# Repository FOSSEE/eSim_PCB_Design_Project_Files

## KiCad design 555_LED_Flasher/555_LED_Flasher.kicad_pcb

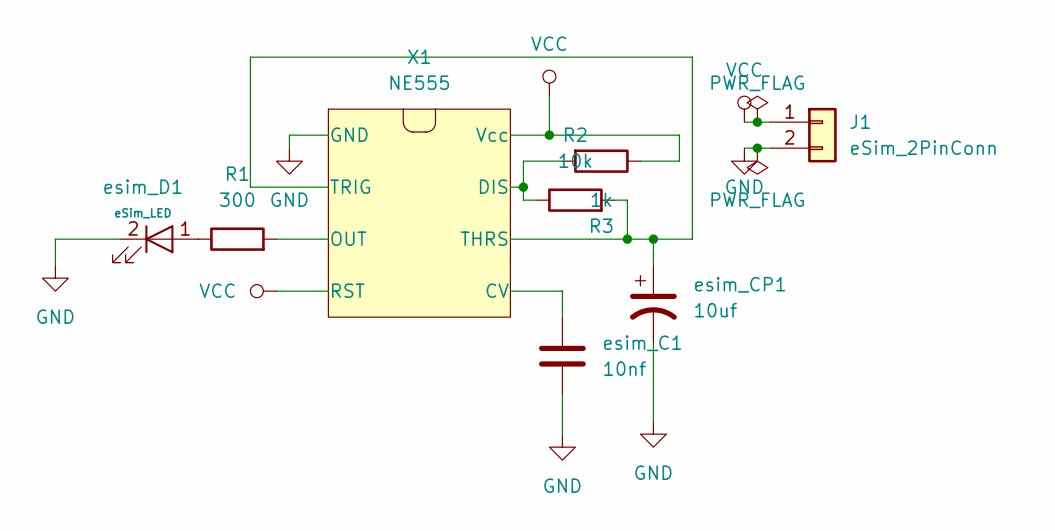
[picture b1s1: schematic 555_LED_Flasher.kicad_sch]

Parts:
J1: eSim_2PinConn; PinHeader_1x02_P2.54mm_Vertical
R1: 300; R_Axial_DIN0207_L6.3mm_D2.5mm_P10.16mm_Horizontal
R2: 10k; R_Axial_DIN0207_L6.3mm_D2.5mm_P10.16mm_Horizontal
R3: 1k; R_Axial_DIN0207_L6.3mm_D2.5mm_P10.16mm_Horizontal
X1: NE555; DIP-8_W7.62mm
esim_C1: 10nf; C_Disc_D5.0mm_W2.5mm_P5.00mm
esim_CP1: 10uf; CP_Radial_D5.0mm_P2.00mm
esim_D1: eSim_LED; LED_D5.0mm_Clear

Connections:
GND: J1.2, X1.1 (GND), esim_C1.2, esim_CP1.2, esim_D1.2 (K)
unnamed: X1.5 (CV), esim_C1.1
unnamed: R2.1, R3.2, X1.7 (DIS)
unnamed: R1.2, X1.3 (OUT)
unnamed: R2.2, X1.2 (TRIG), X1.6 (THRS), esim_CP1.1
unnamed: R1.1, esim_D1.1 (A)
VCC: J1.1, R3.1, X1.4 (RST), X1.8 (Vcc)

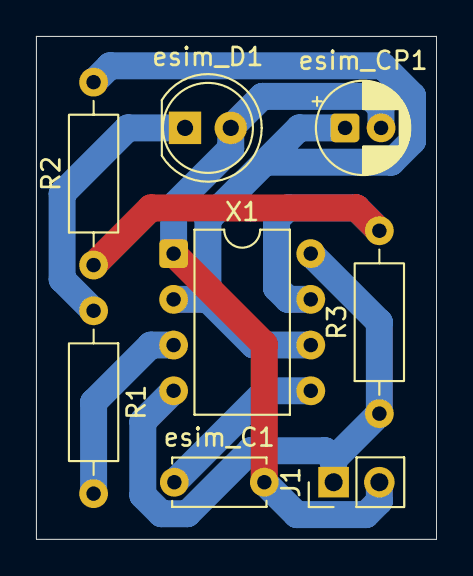
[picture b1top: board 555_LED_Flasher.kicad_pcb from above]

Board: 2 copper layers, 22.2 x 27.9 mm, 8 parts (0 on the bottom side), 7 nets.

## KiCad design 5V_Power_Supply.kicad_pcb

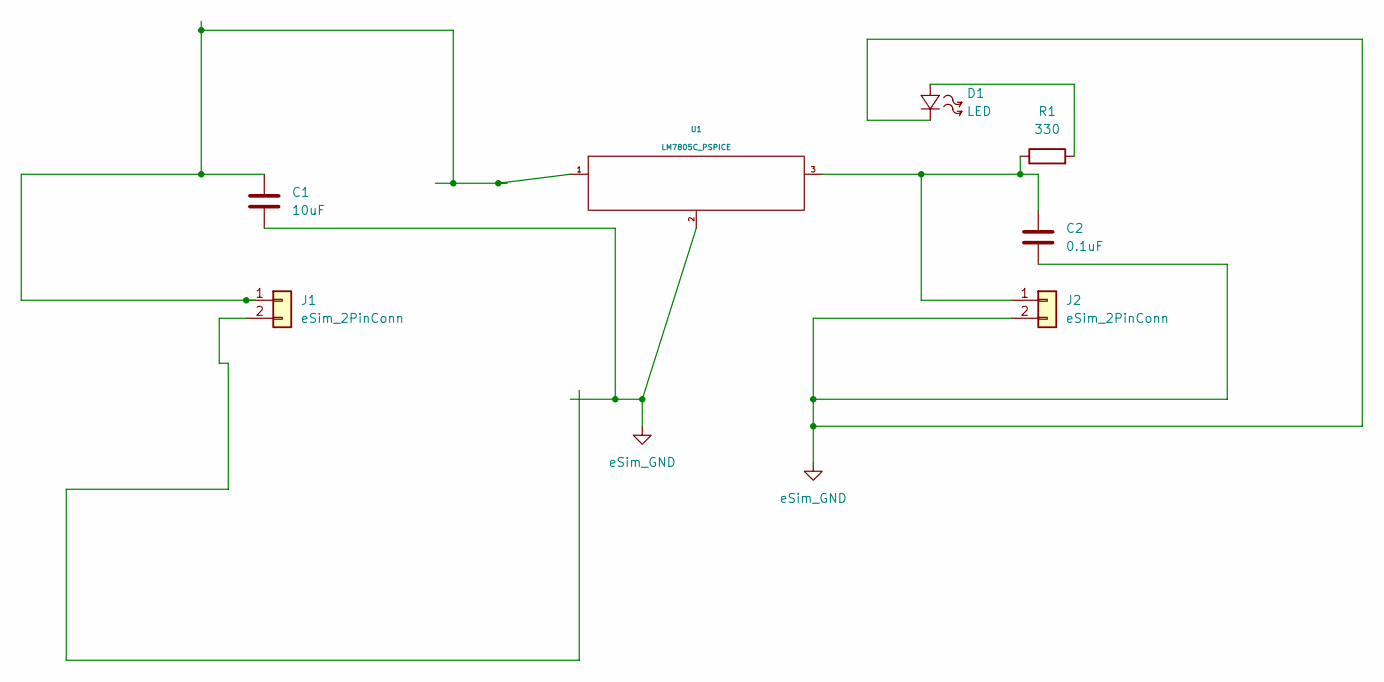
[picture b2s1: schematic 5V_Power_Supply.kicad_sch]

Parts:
C1: 10uF; C_Radial_D5.0mm_H7.0mm_P2.00mm
C2: 0.1uF; C_Disc_D5.0mm_W2.5mm_P5.00mm
D1: LED; LED_D5.0mm_Clear
J1, J2: eSim_2PinConn; PinHeader_1x02_P2.54mm_Vertical
R1: 330; R_Axial_DIN0207_L6.3mm_D2.5mm_P10.16mm_Horizontal
U1: LM7805C_PSPICE; TO-220-3_Vertical

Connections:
GND: C1.2, C2.2, D1.2 (-), J2.2, U1.2
unnamed: C1.1, J1.1, U1.1
unnamed: C2.1, J2.1, R1.1, U1.3
unnamed: D1.1 (+), R1.2

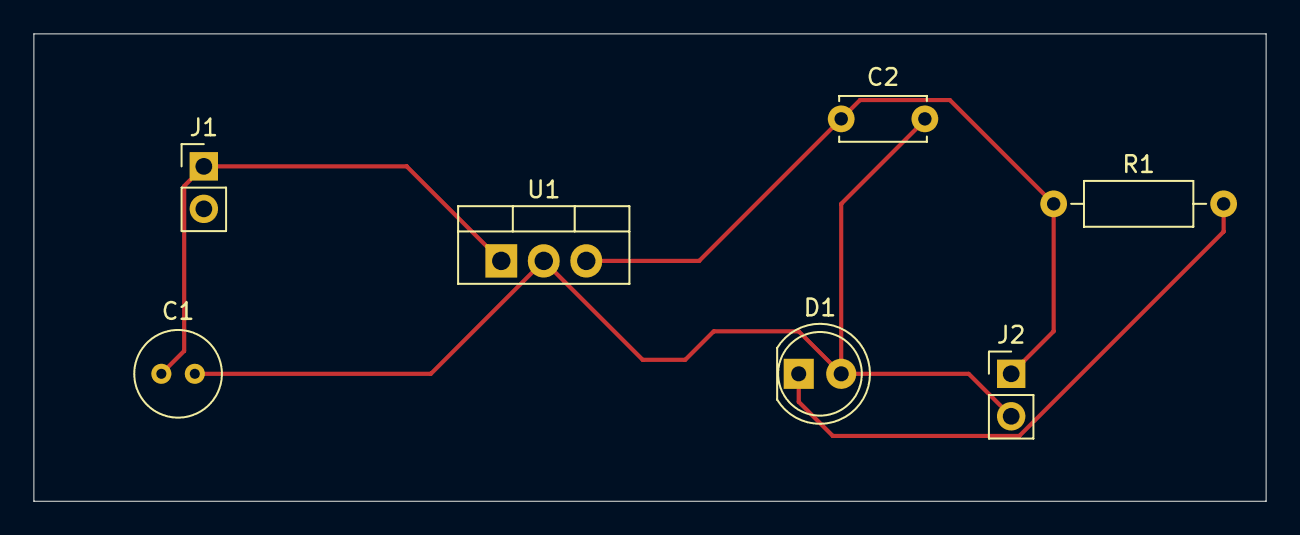
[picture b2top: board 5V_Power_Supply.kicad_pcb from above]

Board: 2 copper layers, 73.7 x 27.9 mm, 7 parts (0 on the bottom side), 4 nets.

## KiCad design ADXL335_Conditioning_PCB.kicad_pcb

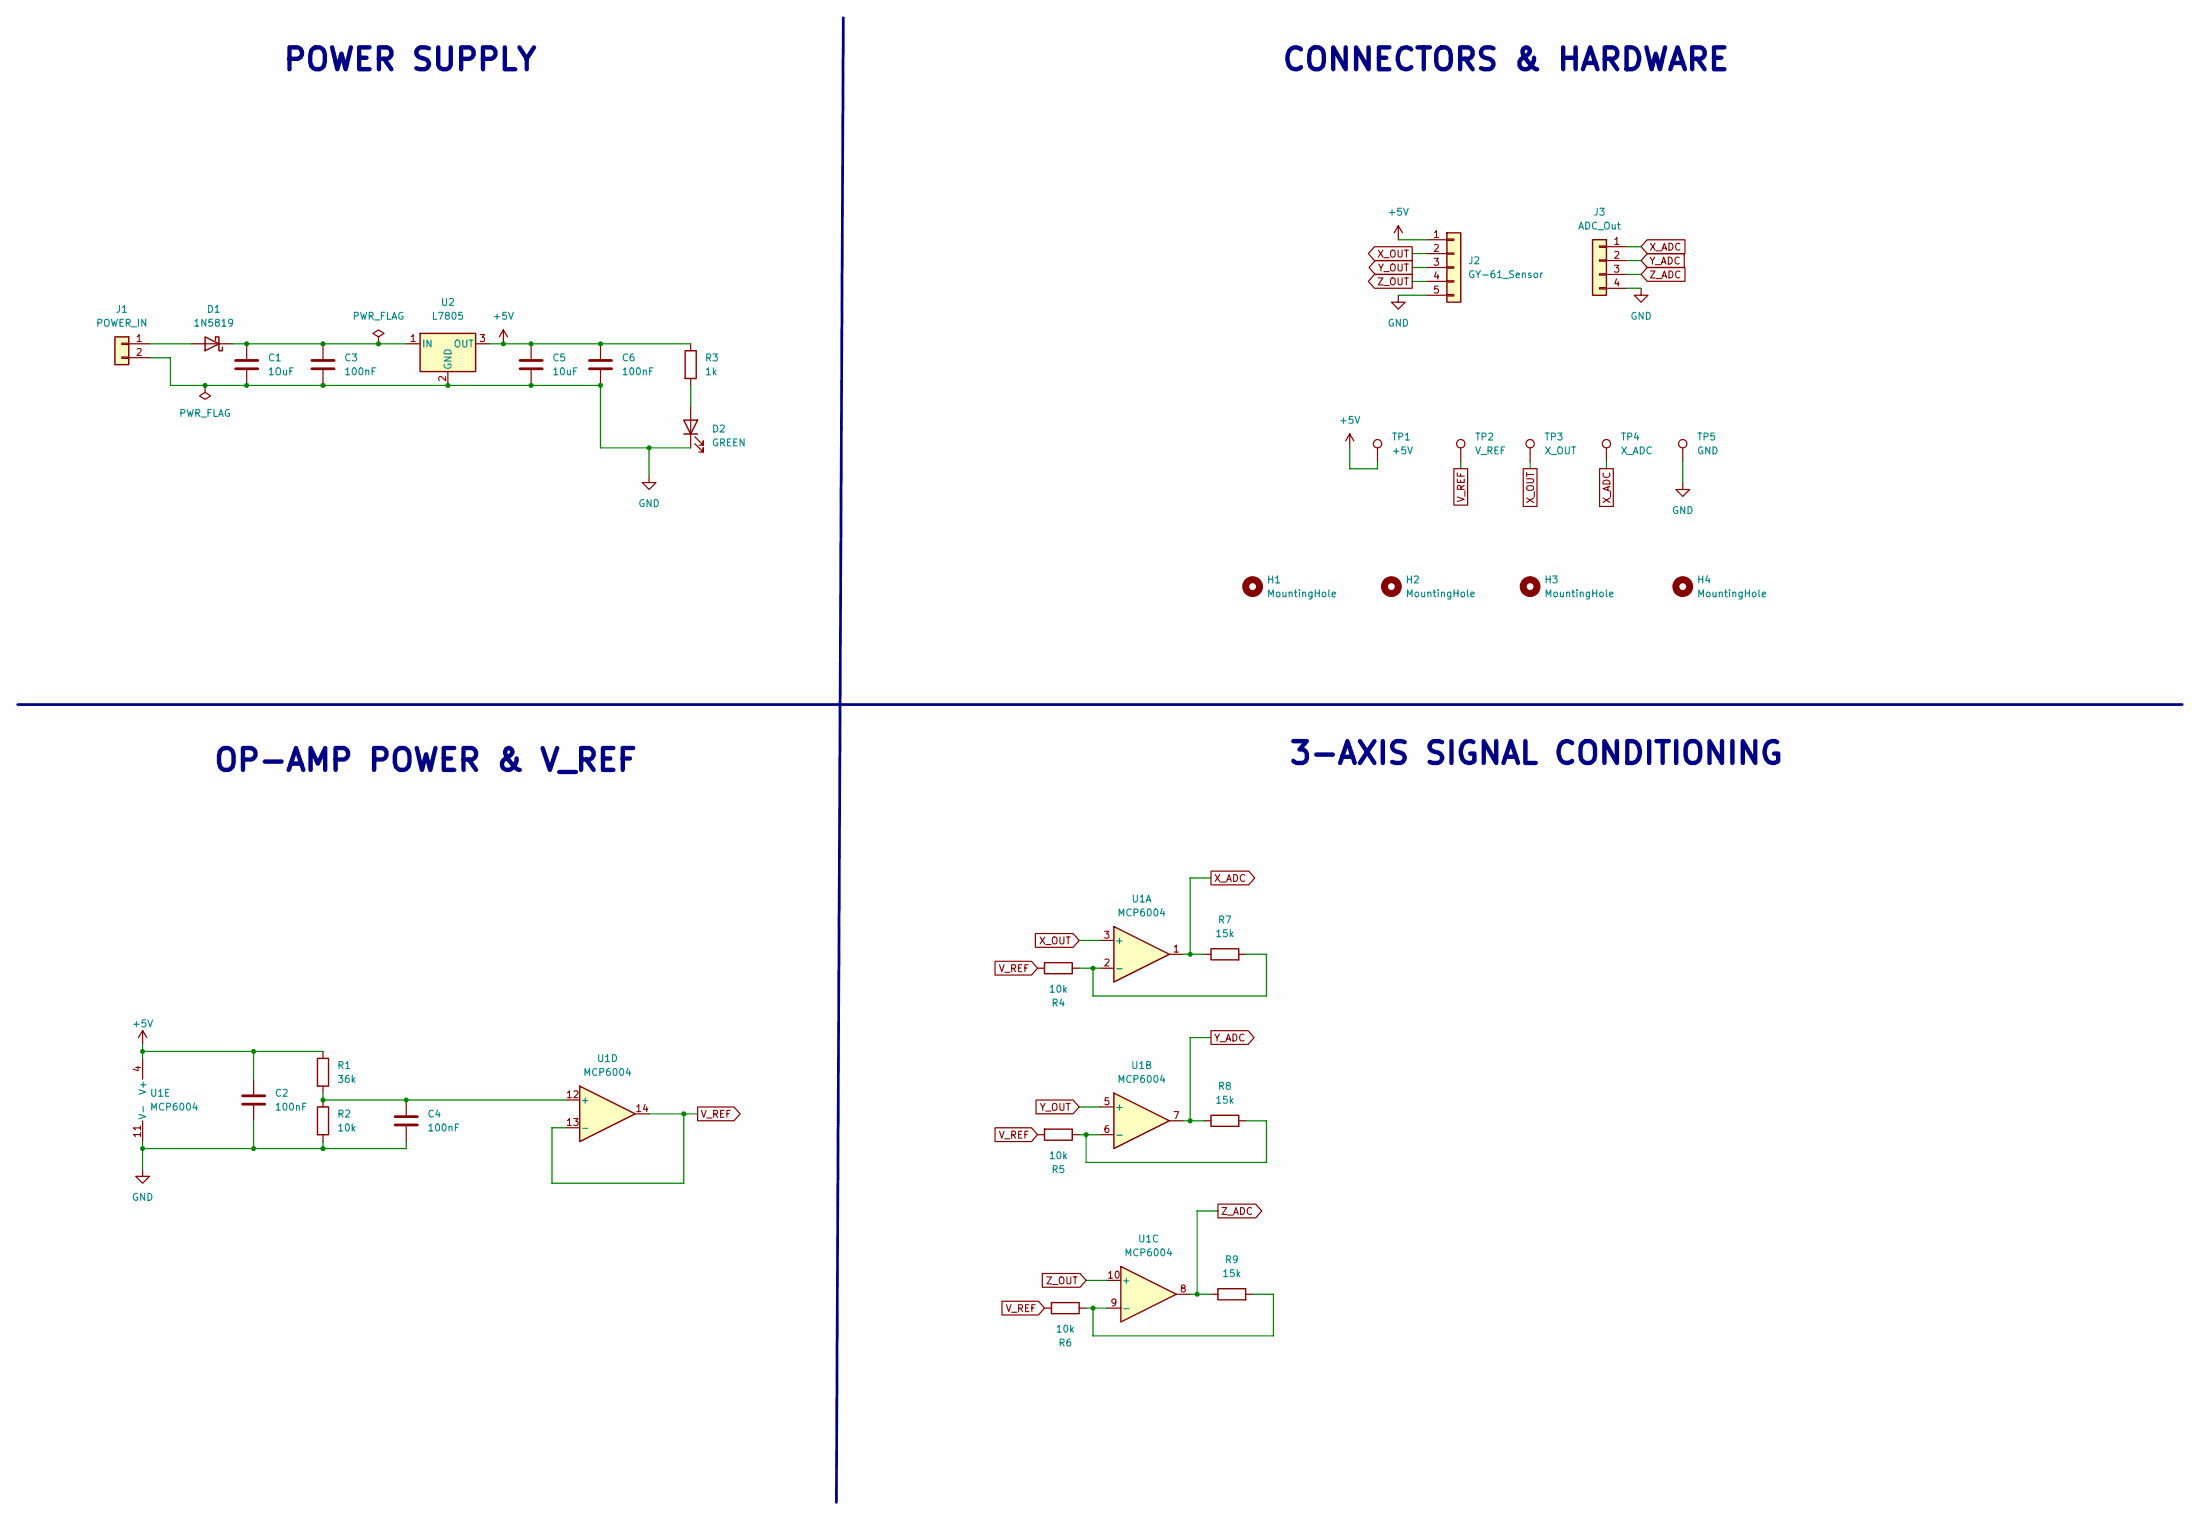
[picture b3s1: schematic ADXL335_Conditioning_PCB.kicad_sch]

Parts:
C1: 1OuF; CP_Elec_5x5.4
C2, C3, C4, C6: 100nF; C_0805_2012Metric_Pad1.18x1.45mm_HandSolder
C5: 10uF; CP_Elec_5x5.4
D1: 1N5819; D_SMA_Handsoldering
D2: GREEN; LED_0805_2012Metric_Pad1.15x1.40mm_HandSolder
H1, H2, H3, H4: MountingHole; MountingHole_3.2mm_M3
J1: POWER_IN; TerminalBlock_Phoenix_MKDS-1,5-2_1x02_P5.00mm_Horizontal
J2: GY-61_Sensor; PinSocket_1x05_P2.54mm_Vertical
J3: ADC_Out; PinHeader_1x04_P2.54mm_Vertical
R1: 36k; R_0805_2012Metric_Pad1.20x1.40mm_HandSolder
R2, R4, R5, R6: 10k; R_0805_2012Metric_Pad1.20x1.40mm_HandSolder
R3: 1k; R_0805_2012Metric_Pad1.20x1.40mm_HandSolder
R7, R8, R9: 15k; R_0805_2012Metric_Pad1.20x1.40mm_HandSolder
TP1: +5V; TestPoint_THTPad_D1.5mm_Drill0.7mm
TP2: V_REF; TestPoint_THTPad_D1.5mm_Drill0.7mm
TP3: X_OUT; TestPoint_THTPad_D1.5mm_Drill0.7mm
TP4: X_ADC; TestPoint_THTPad_D1.5mm_Drill0.7mm
TP5: GND; TestPoint_THTPad_D1.5mm_Drill0.7mm
U1: MCP6004; SOIC-14_3.9x8.7mm_P1.27mm
U2: L7805; TO-252-2

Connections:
+5V: C2.1, C5.1, C6.1, J2.1, R1.1, R3.1, TP1.1, U1.4 (V+), U2.3 (OUT)
GND: C1.2, C2.2, C3.2, C4.2, C5.2, C6.2, D2.1 (K), J1.2, J2.5, J3.4, R2.2, TP5.1, U1.11 (V-), U2.2 (GND)
unnamed: C1.1, C3.1, D1.1 (K), U2.1 (IN)
unnamed: C4.1, R1.2, R2.1, U1.12 (+)
unnamed: D1.2 (A), J1.1
unnamed: D2.2 (A), R3.2
unnamed: R4.1, R7.2, U1.2 (-)
unnamed: R5.1, R8.2, U1.6 (-)
unnamed: R6.1, R9.2, U1.9 (-)
V_REF: R4.2, R5.2, R6.2, TP2.1, U1.13 (-), U1.14
X_ADC: J3.1, R7.1, TP4.1, U1.1
X_OUT: J2.2, TP3.1, U1.3 (+)
Y_ADC: J3.2, R8.1, U1.7
Y_OUT: J2.3, U1.5 (+)
Z_ADC: J3.3, R9.1, U1.8
Z_OUT: J2.4, U1.10 (+)

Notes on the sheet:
OP-AMP POWER & V_REF
CONNECTORS & HARDWARE
POWER SUPPLY
3-AXIS SIGNAL CONDITIONING

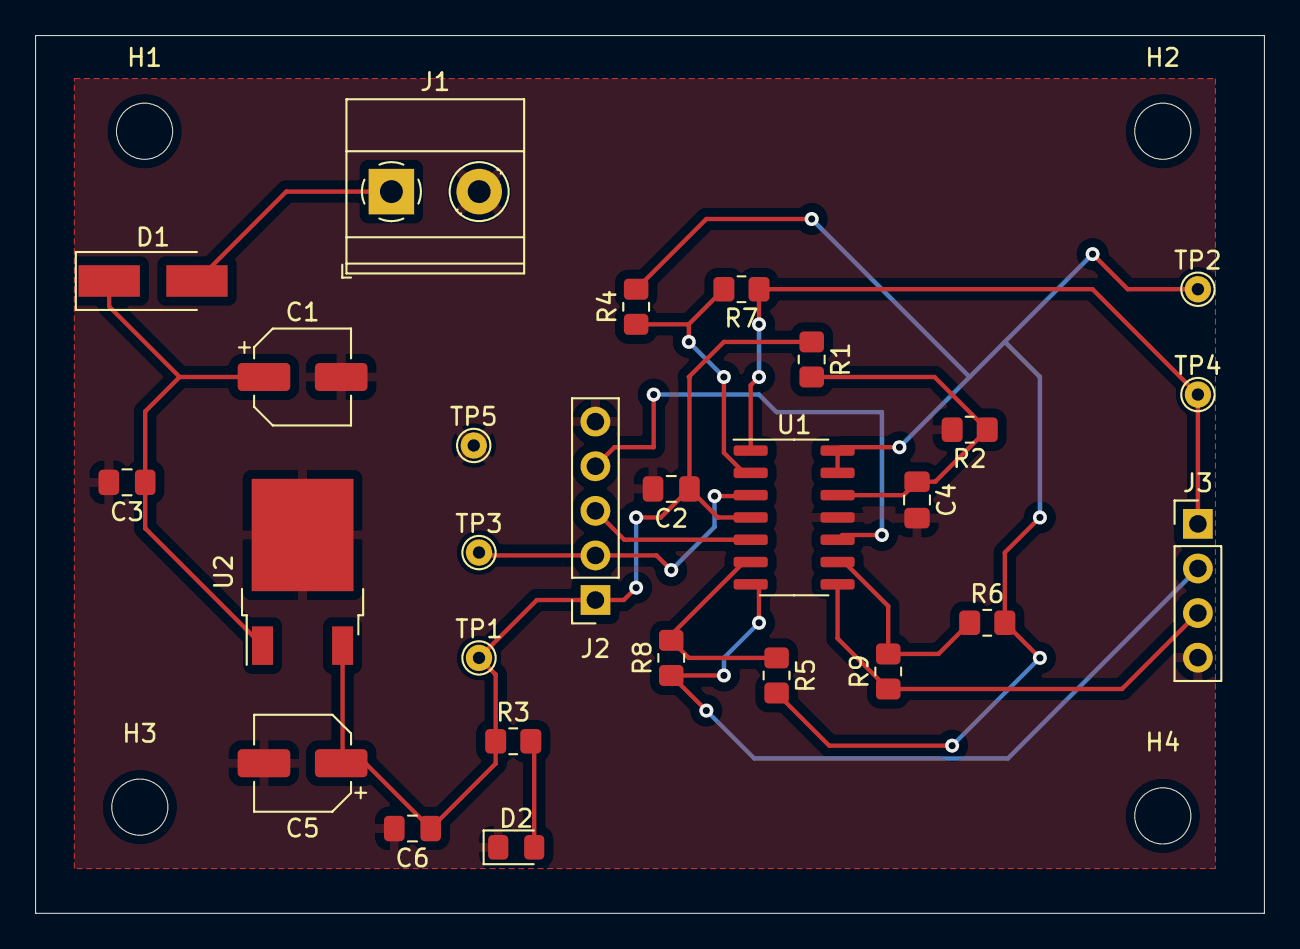
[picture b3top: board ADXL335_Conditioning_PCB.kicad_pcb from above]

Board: 2 copper layers, 70.0 x 50.0 mm, 31 parts (0 on the bottom side), 16 nets.

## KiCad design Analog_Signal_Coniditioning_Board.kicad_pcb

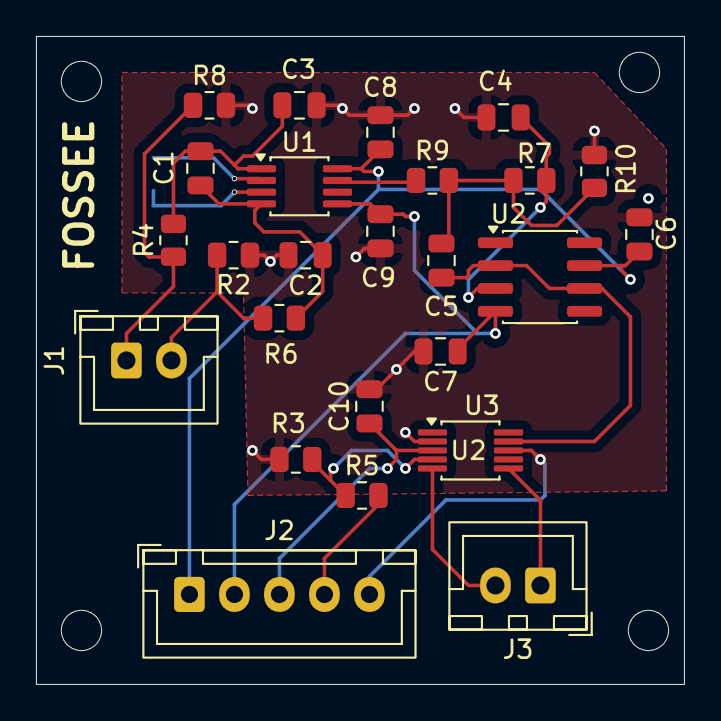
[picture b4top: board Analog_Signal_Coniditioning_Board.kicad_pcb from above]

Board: 2 copper layers, 36.0 x 36.0 mm, 26 parts (1 on the bottom side), 18 nets.

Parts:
C1: 1nf; C_0805_2012Metric
C2, C3: 100pf; C_0805_2012Metric
C4: 0.01uf; C_0805_2012Metric
C5: 0.068uf; C_0805_2012Metric
C6, C7, C8, C9, C10: 0.1uf; C_0805_2012Metric
J1, J3: Screw_Terminal_01x02; JST_XH_B2B-XH-A_1x02_P2.50mm_Vertical
J2: Screw_Terminal_01x05; JST_XH_B5B-XH-A_1x05_P2.50mm_Vertical
R1: Rg; R_0805_2012Metric
R2, R8: 10M; R_0805_2012Metric
R3, R5: 10k; R_0805_2012Metric
R4, R6: 4.7k; R_0805_2012Metric
R7: 33k; R_0805_2012Metric
R9, R10: 20k; R_0805_2012Metric
U1: AD8421; MSOP-8_3x3mm_P0.65mm
U2: TL081; SOIC-8_3.9x4.9mm_P1.27mm
U2#2: AD8475xRMZ; MSOP-10_3x3mm_P0.5mm

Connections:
+5V: C10.1, J2.3, U2#2.3 (+Vs)
+15V: C6.1, C8.1, J2.1, U1.8 (Vs+), U2.7 (V+)
-15V: C7.1, C9.1, J2.2, U1.5 (Vs-), U2.4 (V-)
AD8421_op: R9.1, U1.7
ADC_ref: J2.4, R5.2
GND: C2.2, C3.1, C4.2, C6.2, C7.2, C8.2, C9.2, C10.2, J2.5, R2.1, R3.2, R8.2, R10.1, U2#2.2 (-IN0.4x), U2#2.8 (-Vs)
unnamed: C5.1, R7.1, R9.2, R10.2
unnamed: R1.1, U1.3 (Rg)
unnamed: R1.2, U1.2 (Rg)
unnamed: C1.2, C2.1, R6.2, U1.4 (+)
unnamed: C1.1, C3.2, R4.2, U1.1 (-)
unnamed: C4.1, R7.2, U2.3 (+)
TL081-0p: C5.2, U2.2 (-), U2.6, U2#2.9 (+IN0.4x)
Vin+: J1.1, R4.1, R8.1
Vin-: J1.2, R2.2, R6.1
Vout+: J3.2, U2#2.5 (+)
Vout-: J3.1, U2#2.6 (-)
vocm: R3.1, R5.1, U2#2.4 (VOCM)

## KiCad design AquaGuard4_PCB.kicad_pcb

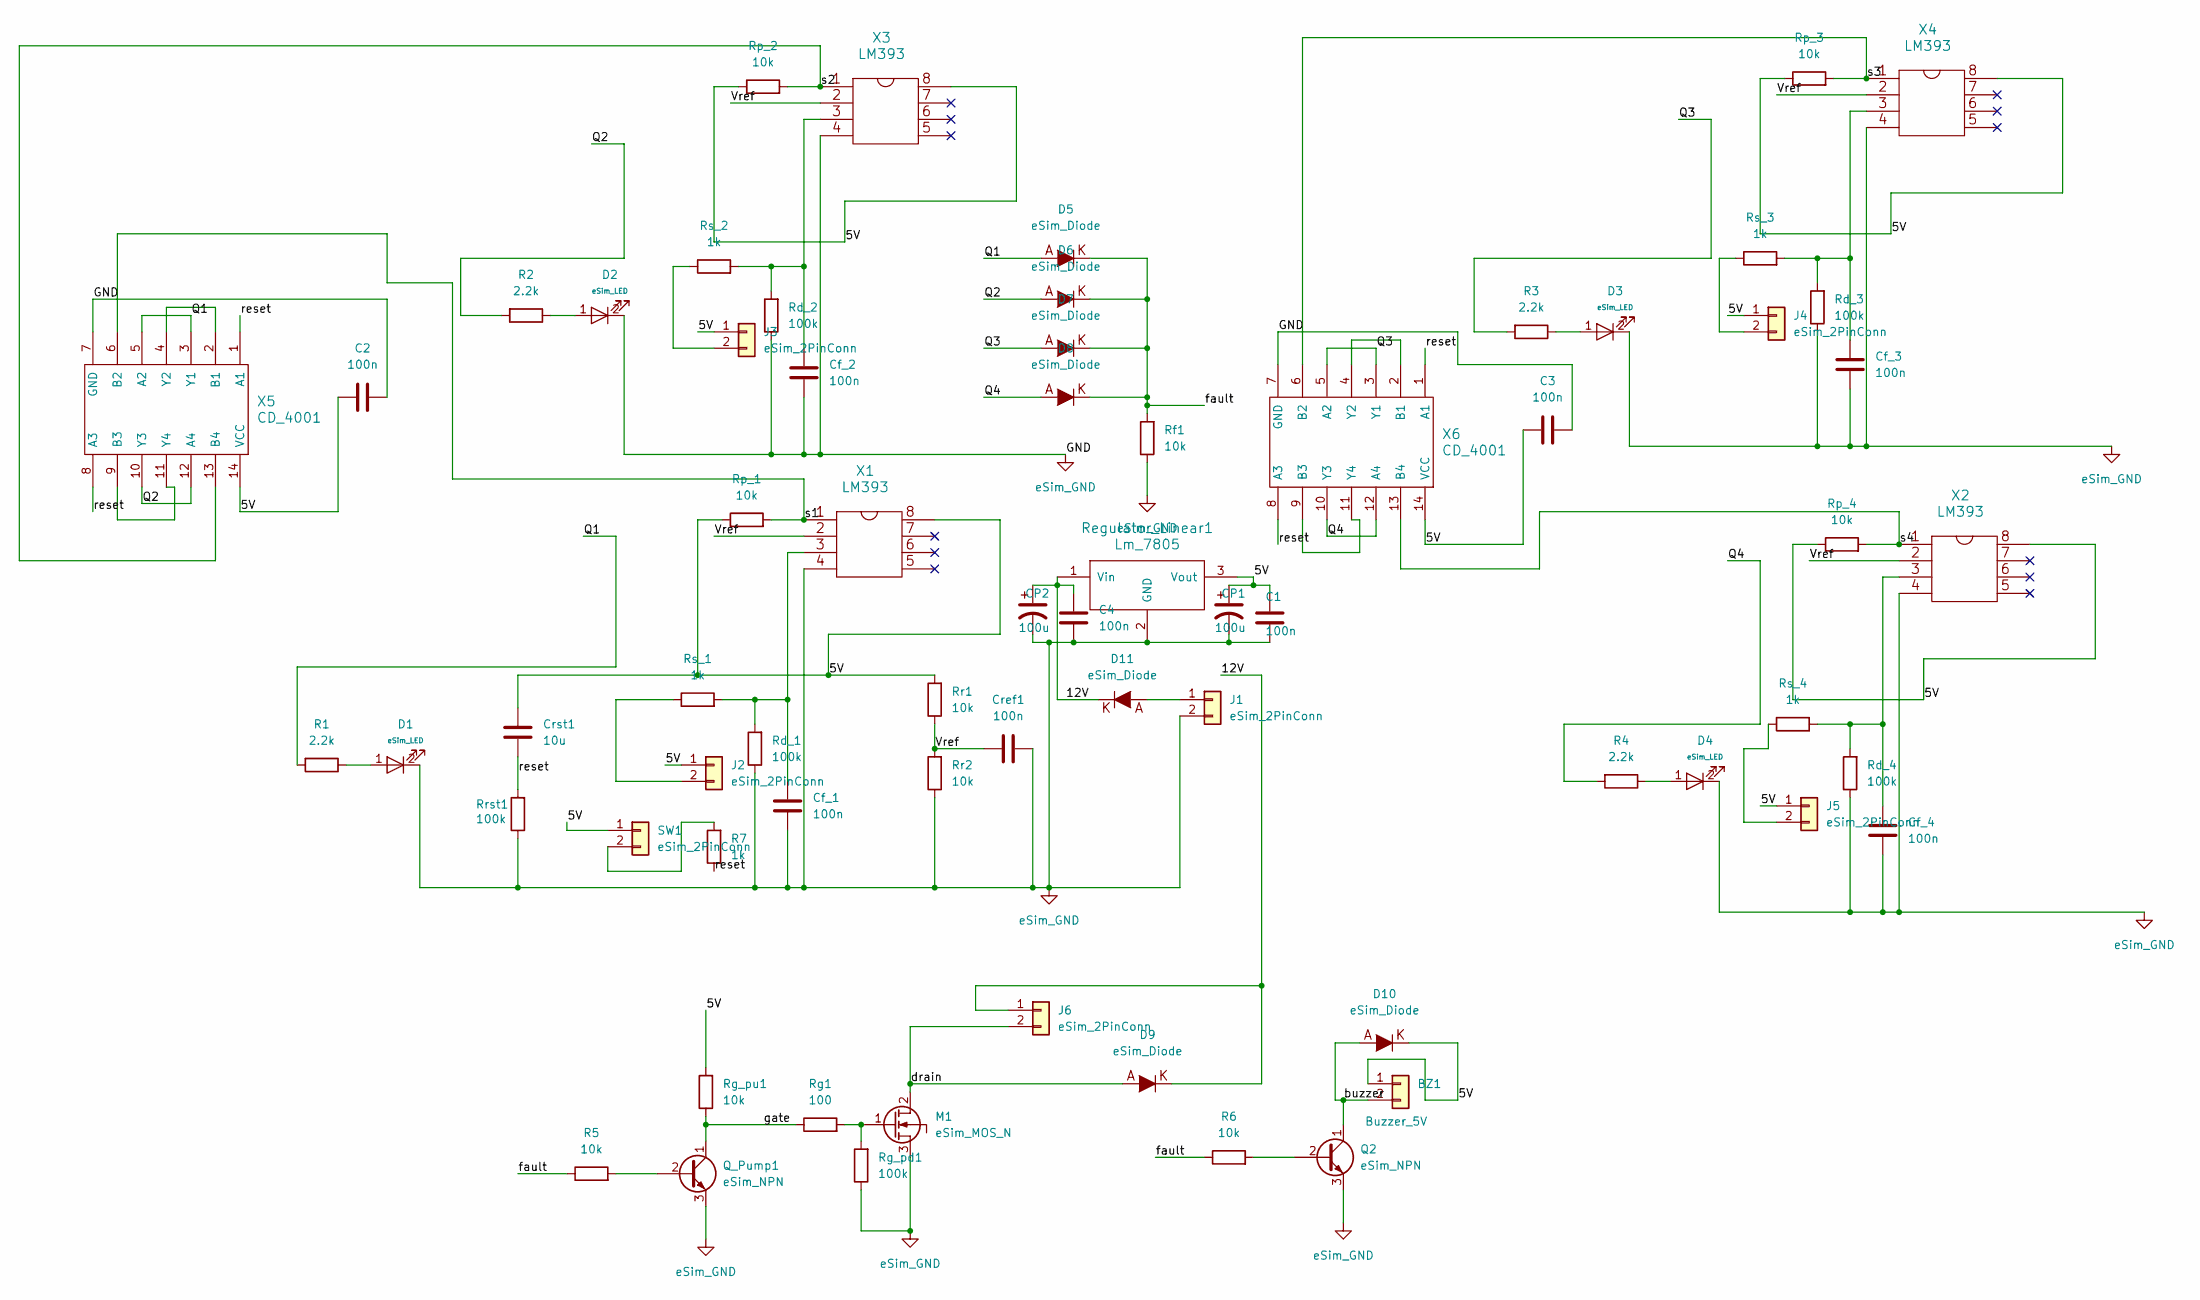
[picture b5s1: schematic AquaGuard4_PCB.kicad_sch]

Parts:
BZ1: Buzzer_5V; PinHeader_1x02_P2.54mm_Vertical
C1, C2, C3, C4: 100n; C_Disc_D5.0mm_W2.5mm_P5.00mm
CP1, CP2: 100u; CP_Radial_D6.3mm_P2.50mm
Cf_1, Cf_2, Cf_3, Cf_4: 100n; C_Disc_D5.0mm_W2.5mm_P5.00mm
Cref1: 100n; C_Disc_D5.0mm_W2.5mm_P5.00mm
Crst1: 10u; CP_Radial_D6.3mm_P2.50mm
D1, D2, D3, D4: eSim_LED; LED_D5.0mm
D5, D6, D7, D8: eSim_Diode; D_DO-35_SOD27_P7.62mm_Horizontal
D9, D10, D11: eSim_Diode; D_DO-41_SOD81_P10.16mm_Horizontal
J1, J2, J3, J4, J5, J6: eSim_2PinConn; PinHeader_1x02_P2.54mm_Vertical
M1: eSim_MOS_N; TO-220-3_Vertical
Q2: eSim_NPN; TO-92_Inline
Q_Pump1: eSim_NPN; TO-92_Inline
R1, R2, R3, R4: 2.2k; R_Axial_DIN0207_L6.3mm_D2.5mm_P10.16mm_Horizontal
R5, R6: 10k; R_Axial_DIN0207_L6.3mm_D2.5mm_P10.16mm_Horizontal
R7: 1k; R_Axial_DIN0207_L6.3mm_D2.5mm_P10.16mm_Horizontal
Rd_1, Rd_2, Rd_3, Rd_4: 100k; R_Axial_DIN0207_L6.3mm_D2.5mm_P10.16mm_Horizontal
Regulator_Linear1: Lm_7805; TO-220-3_Vertical
Rf1: 10k; R_Axial_DIN0207_L6.3mm_D2.5mm_P10.16mm_Horizontal
Rg1: 100; R_Axial_DIN0207_L6.3mm_D2.5mm_P10.16mm_Horizontal
Rg_pd1: 100k; R_Axial_DIN0207_L6.3mm_D2.5mm_P10.16mm_Horizontal
Rg_pu1: 10k; R_Axial_DIN0207_L6.3mm_D2.5mm_P10.16mm_Horizontal
Rp_1, Rp_2, Rp_3, Rp_4: 10k; R_Axial_DIN0207_L6.3mm_D2.5mm_P10.16mm_Horizontal
Rr1, Rr2: 10k; R_Axial_DIN0207_L6.3mm_D2.5mm_P10.16mm_Horizontal
Rrst1: 100k; R_Axial_DIN0207_L6.3mm_D2.5mm_P10.16mm_Horizontal
Rs_1, Rs_2, Rs_3, Rs_4: 1k; R_Axial_DIN0207_L6.3mm_D2.5mm_P10.16mm_Horizontal
SW1: eSim_2PinConn; PinHeader_1x02_P2.54mm_Vertical
X1, X2, X3, X4: LM393; DIP-8_W7.62mm
X5, X6: CD_4001; DIP-14_W7.62mm

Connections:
/5V: BZ1.1, C1.1, C2.1, C3.1, CP1.1, Crst1.1, D10.2 (K), J2.1, J3.1, J4.1, J5.1, Regulator_Linear1.3 (Vout), Rg_pu1.2, Rp_1.1, Rp_2.1, Rp_3.1, Rp_4.1, Rr1.2, SW1.1, X1.1 (8), X2.1 (8), X3.1 (8), X4.1 (8), X5.14 (VCC), X6.14 (VCC)
/12V: C4.1, CP2.1, D9.2 (K), D11.2 (K), J6.1, Regulator_Linear1.1 (Vin)
/Q1: D5.1 (A), R1.2, X5.3 (Y1), X5.5 (A2)
/Q2: D6.1 (A), R2.2, X5.10 (Y3), X5.12 (A4)
/Q3: D7.1 (A), R3.2, X6.3 (Y1), X6.5 (A2)
/Q4: D8.1 (A), R4.2, X6.10 (Y3), X6.12 (A4)
/Vref: Cref1.1, Rr1.1, Rr2.2, X1.3 (2), X2.3 (2), X3.3 (2), X4.3 (2)
/buzzer: BZ1.2, D10.1 (A), Q2.1 (C)
/drain: D9.1 (A), J6.2, M1.2 (D)
/fault: D5.2 (K), D6.2 (K), D7.2 (K), D8.2 (K), R5.1, R6.1, Rf1.2
/gate: Q_Pump1.1 (C), Rg1.1, Rg_pu1.1
/reset: Crst1.2, R7.1, Rrst1.2, X5.1 (A1), X5.8 (A3), X6.1 (A1), X6.8 (A3)
/s1: Rp_1.2, X1.4 (1), X5.6 (B2)
/s2: Rp_2.2, X3.4 (1), X5.13 (B4)
/s3: Rp_3.2, X4.4 (1), X6.6 (B2)
/s4: Rp_4.2, X2.4 (1), X6.13 (B4)
unnamed: D1.1 (A), R1.1
unnamed: D2.1 (A), R2.1
unnamed: D3.1 (A), R3.1
unnamed: D4.1 (A), R4.1
unnamed: D11.1 (A), J1.1
unnamed: J2.2, Rs_1.1
unnamed: J3.2, Rs_2.1
unnamed: J4.2, Rs_3.1
unnamed: J5.2, Rs_4.1
unnamed: M1.1 (G), Rg1.2, Rg_pd1.2
unnamed: Q2.2 (B), R6.2
unnamed: Q_Pump1.2 (B), R5.2
unnamed: R7.2, SW1.2
unnamed: Cf_1.1, Rd_1.2, Rs_1.2, X1.2 (3)
unnamed: Cf_4.1, Rd_4.2, Rs_4.2, X2.2 (3)
unnamed: Cf_2.1, Rd_2.2, Rs_2.2, X3.2 (3)
unnamed: Cf_3.1, Rd_3.2, Rs_3.2, X4.2 (3)
unnamed: X5.2 (B1), X5.4 (Y2)
unnamed: X5.9 (B3), X5.11 (Y4)
unnamed: X6.2 (B1), X6.4 (Y2)
unnamed: X6.9 (B3), X6.11 (Y4)
eSim_GND: C1.2, C2.2, C3.2, C4.2, CP1.2, CP2.2, Cf_1.2, Cf_2.2, Cf_3.2, Cf_4.2, Cref1.2, D1.2 (K), D2.2 (K), D3.2 (K), D4.2 (K), J1.2, M1.3 (S), Q2.3 (E), Q_Pump1.3 (E), Rd_1.1, Rd_2.1, Rd_3.1, Rd_4.1, Regulator_Linear1.2 (GND), Rf1.1, Rg_pd1.1, Rr2.1, Rrst1.1, X1.5 (4), X2.5 (4), X3.5 (4), X4.5 (4), X5.7 (GND), X6.7 (GND)

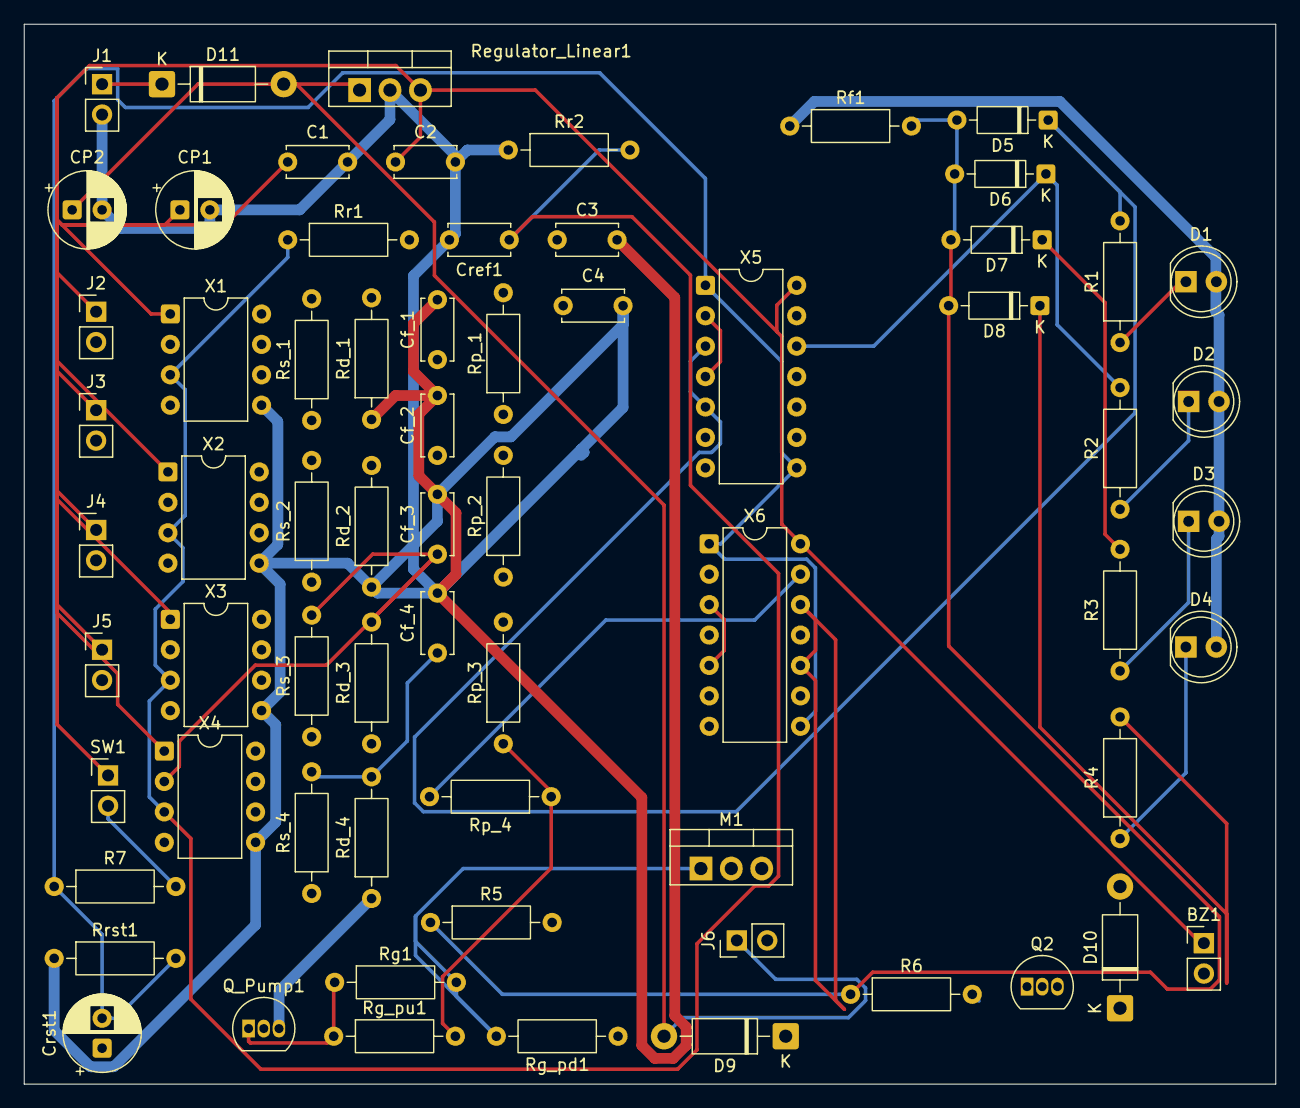
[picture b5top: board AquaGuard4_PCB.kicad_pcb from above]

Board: 2 copper layers, 104.5 x 88.5 mm, 67 parts (0 on the bottom side), 38 nets.

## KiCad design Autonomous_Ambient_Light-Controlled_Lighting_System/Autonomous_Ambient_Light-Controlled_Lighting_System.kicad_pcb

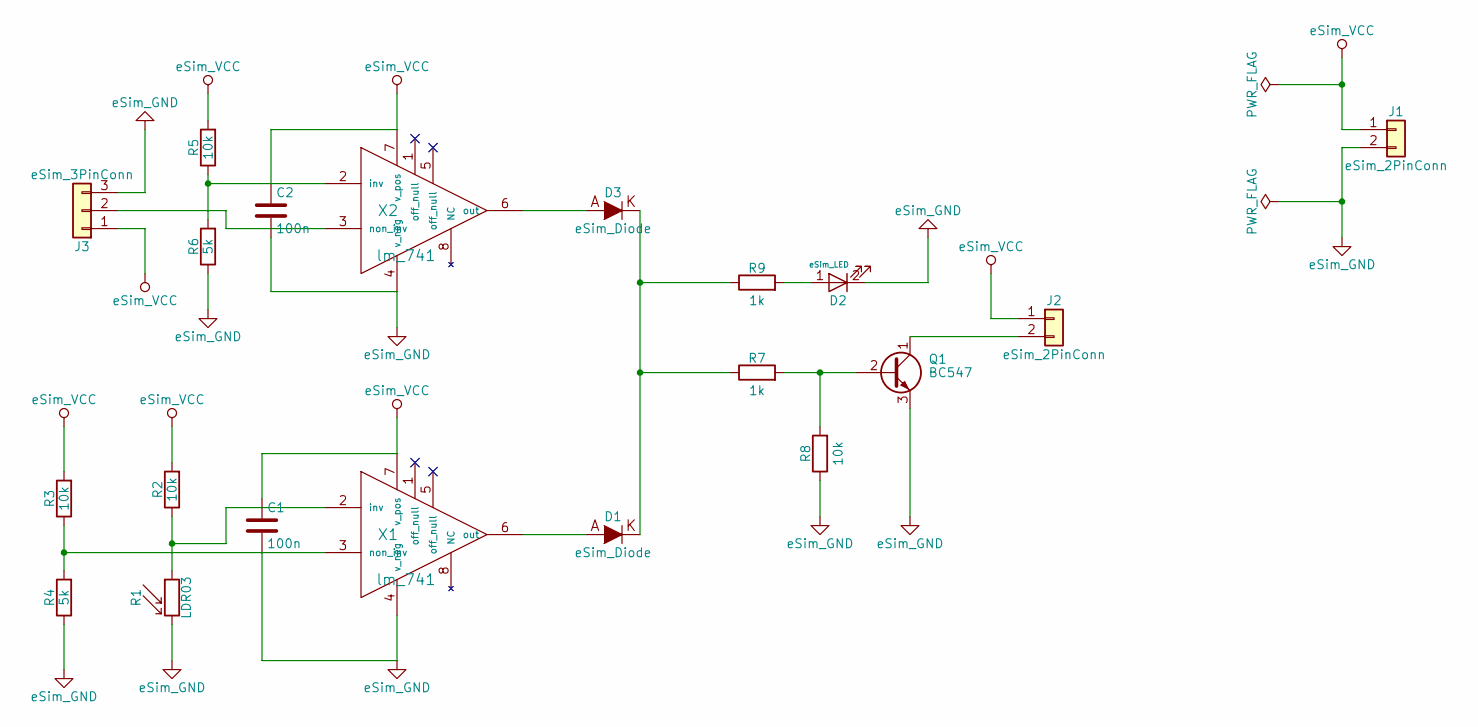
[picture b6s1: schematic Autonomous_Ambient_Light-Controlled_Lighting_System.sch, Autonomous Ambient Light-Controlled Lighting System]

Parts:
C1, C2: 100n; C_Disc_D5.0mm_W2.5mm_P5.00mm
D1, D3: eSim_Diode; D_DO-35_SOD27_P7.62mm_Horizontal
D2: eSim_LED; LED_D5.0mm
J1, J2: eSim_2PinConn; Pin_Header_Straight_1x02_Pitch2.54mm
J3: eSim_3PinConn; Pin_Header_Straight_1x03_Pitch2.54mm
Q1: BC547; TO-92_Molded_Narrow
R1: LDR03; Resistor_LDR_10x8.5_RM7.6
R2, R3, R5, R8: 10k; R_Axial_DIN0207_L6.3mm_D2.5mm_P7.62mm_Horizontal
R4, R6: 5k; R_Axial_DIN0207_L6.3mm_D2.5mm_P7.62mm_Horizontal
R7, R9: 1k; R_Axial_DIN0207_L6.3mm_D2.5mm_P7.62mm_Horizontal
X1, X2: lm_741; DIP-8_W7.62mm

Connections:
GND: C1.2, C2.2, D2.2 (K), J1.2, J3.3, Q1.3 (E), R1.2, R4.1, R6.1, R8.1, X1.4 (v_neg), X2.4 (v_neg)
unnamed: D1.1 (A), X1.6 (out)
unnamed: D1.2 (K), D3.2 (K), R7.1, R9.1
unnamed: D2.1 (A), R9.2
unnamed: D3.1 (A), X2.6 (out)
unnamed: J2.2, Q1.1 (C)
unnamed: J3.2, X2.3 (non_inv)
unnamed: Q1.2 (B), R7.2, R8.2
unnamed: R1.1, R2.1, X1.2 (inv)
unnamed: R3.1, R4.2, X1.3 (non_inv)
unnamed: R5.1, R6.2, X2.2 (inv)
VCC: C1.1, C2.1, J1.1, J2.1, J3.1, R2.2, R3.2, R5.2, X1.7 (v_pos), X2.7 (v_pos)

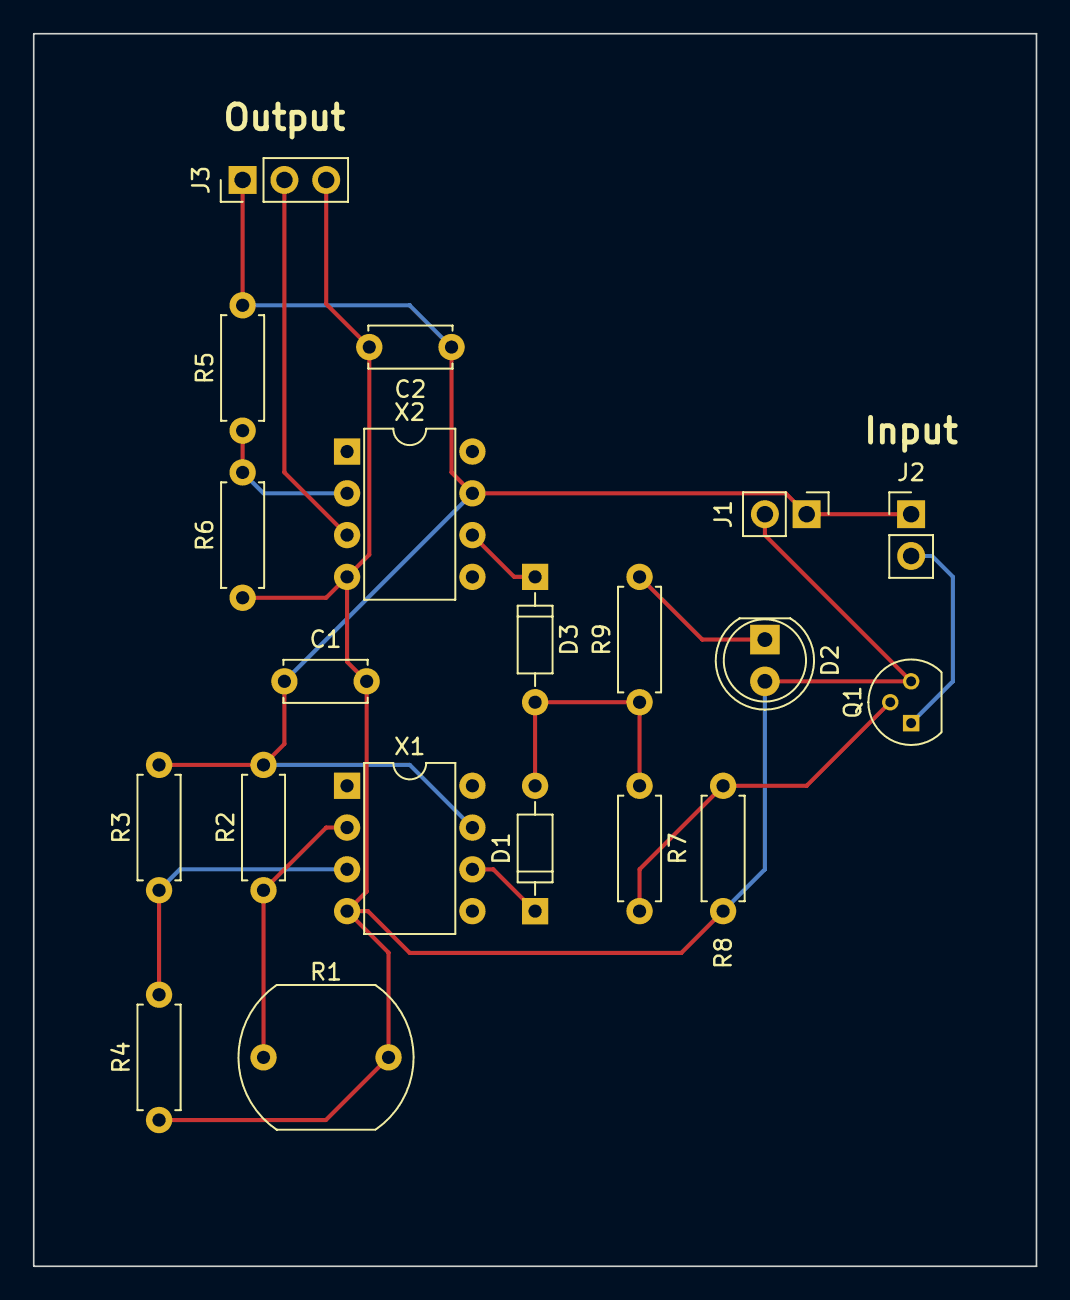
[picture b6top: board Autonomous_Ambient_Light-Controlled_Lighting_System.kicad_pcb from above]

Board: 4 copper layers, 61.0 x 74.9 mm, 20 parts (0 on the bottom side), 12 nets.
